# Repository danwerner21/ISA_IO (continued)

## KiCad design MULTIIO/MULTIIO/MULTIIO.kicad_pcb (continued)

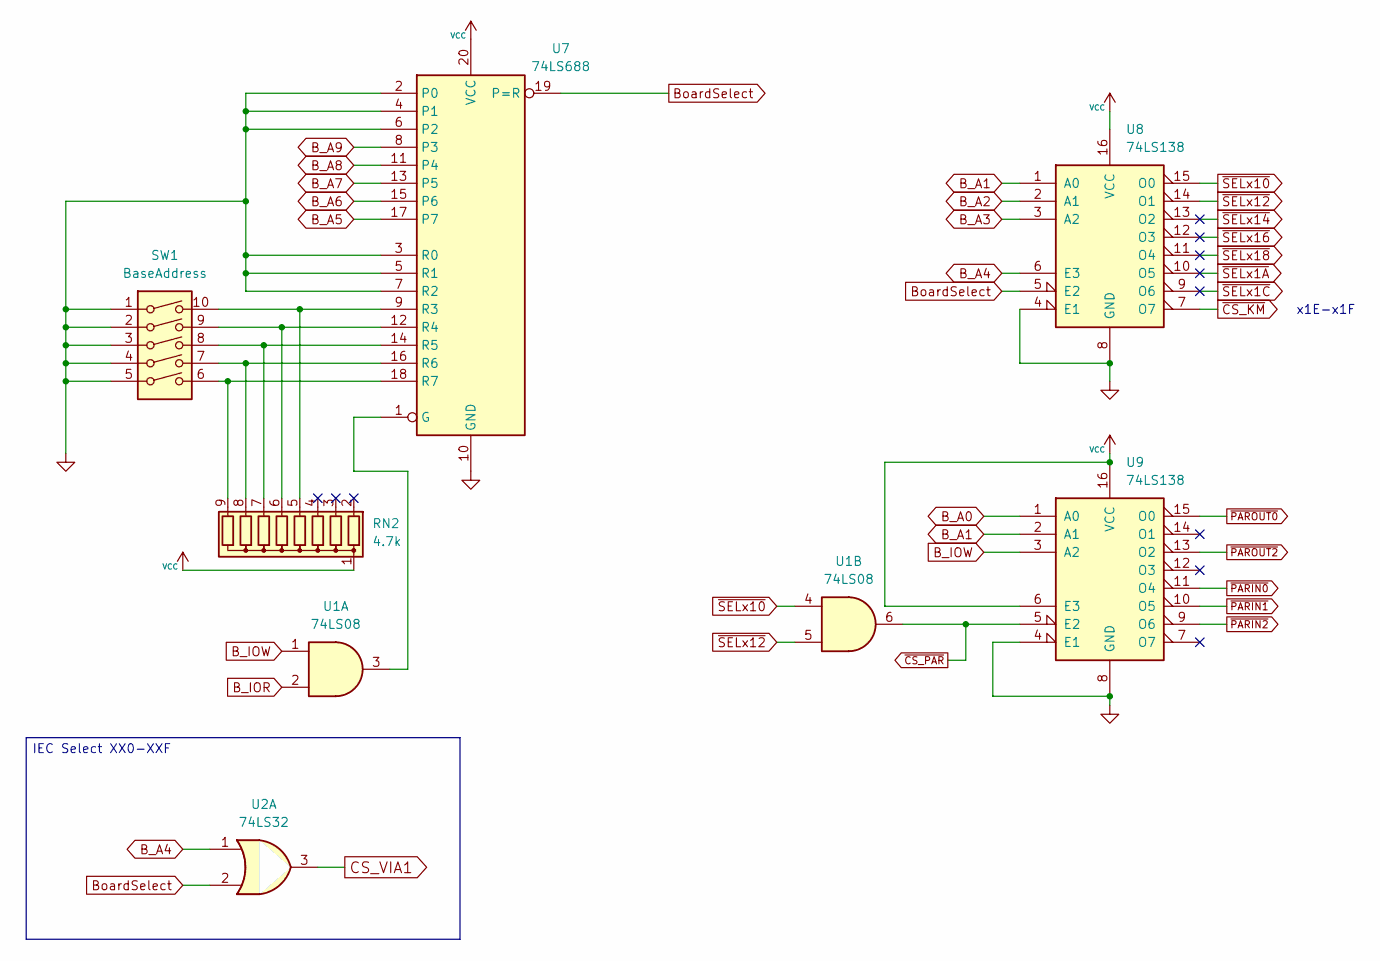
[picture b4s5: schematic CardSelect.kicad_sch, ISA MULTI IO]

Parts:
RN2: 4.7k; STD_DDW_SIP9
SW1: BaseAddress; STD_DDW_DIP10
U1: 74LS08; STD_DDW_DIP14
U2: 74LS32; STD_DDW_DIP14
U7: 74LS688; STD_DDW_DIP20
U8, U9: 74LS138; STD_DDW_DIP16

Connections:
B_A0: U9.1 (A0); also elsewhere on the board
B_A1: U8.1 (A0), U9.2 (A1); also elsewhere on the board
B_A2: U8.2 (A1); also elsewhere on the board
B_A3: U8.3 (A2); also elsewhere on the board
B_A4: U2.1, U8.6 (E3); also elsewhere on the board
B_A5: U7.17 (P7); also elsewhere on the board
B_A6: U7.15 (P6); also elsewhere on the board
B_A7: U7.13 (P5); also elsewhere on the board
B_A8: U7.11 (P4); also elsewhere on the board
B_A9: U7.8 (P3); also elsewhere on the board
B_IOR: U1.2; also elsewhere on the board
B_IOW: U1.1, U9.3 (A2); also elsewhere on the board
BoardSelect: U2.2, U7.19 (P=R), U8.5 (E2)
CS_VIA1: U2.3; also elsewhere on the board
GND: SW1.1, SW1.2, SW1.3, SW1.4, SW1.5, U7.2 (P0), U7.3 (R0), U7.4 (P1), U7.5 (R1), U7.6 (P2), U7.7 (R2), U7.10 (GND), U8.4 (E1), U8.8 (GND), U9.4 (E1), U9.8 (GND); also elsewhere on the board
unnamed: RN2.5 (R4), SW1.10, U7.9 (R3)
unnamed: RN2.6 (R5), SW1.9, U7.12 (R4)
unnamed: RN2.7 (R6), SW1.8, U7.14 (R5)
unnamed: RN2.8 (R7), SW1.7, U7.16 (R6)
unnamed: RN2.9 (R8), SW1.6, U7.18 (R7)
unnamed: U1.3, U7.1 (G)
VCC: RN2.1 (common), U7.20 (VCC), U8.16 (VCC), U9.6 (E3), U9.16 (VCC); also elsewhere on the board
~CS_KM: U8.7 (O7); also elsewhere on the board
~CS_PAR: U1.6, U9.5 (E2); also elsewhere on the board
~PARIN0: U9.11 (O4); also elsewhere on the board
~PARIN1: U9.10 (O5); also elsewhere on the board
~PARIN2: U9.9 (O6); also elsewhere on the board
~PAROUT0: U9.15 (O0); also elsewhere on the board
~PAROUT2: U9.13 (O2); also elsewhere on the board
~SELx1A: U8.10 (O5)
~SELx1C: U8.9 (O6)
~SELx10: U1.4, U8.15 (O0)
~SELx12: U1.5, U8.14 (O1)
~SELx14: U8.13 (O2)
~SELx16: U8.12 (O3)
~SELx18: U8.11 (O4)

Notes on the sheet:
IEC Select XX0-XXF
x1E-x1F

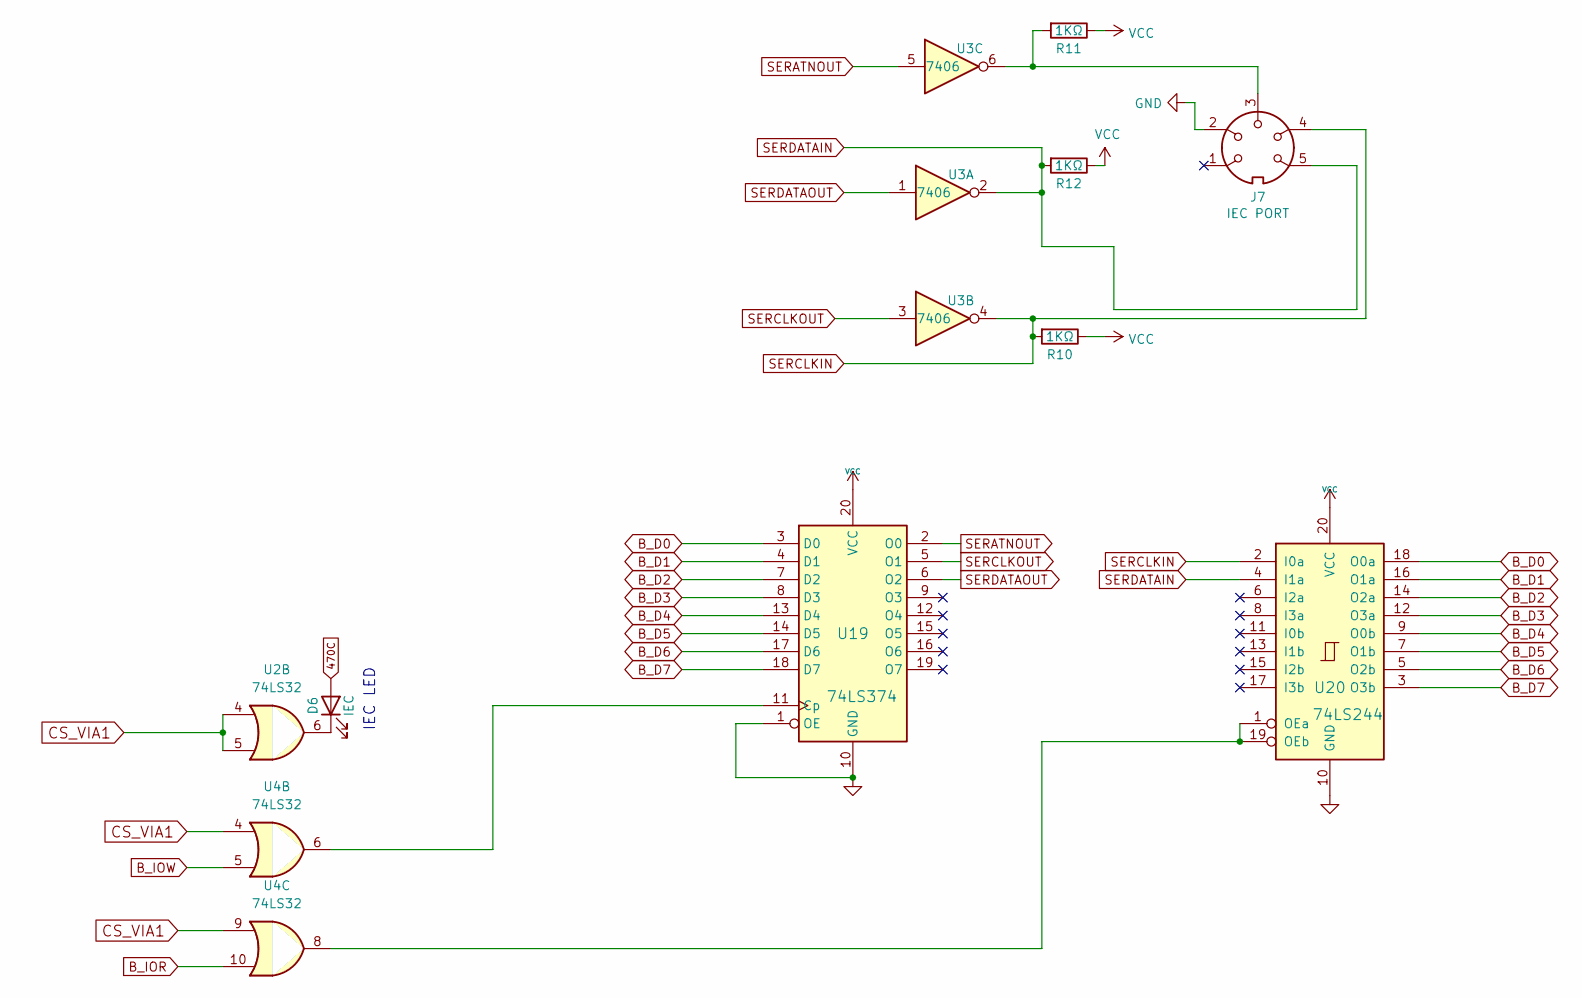
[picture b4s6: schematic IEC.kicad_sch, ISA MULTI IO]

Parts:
D6: IEC; STD_DDW_LED5
J7: IEC PORT; iec_din6
R10, R11, R12: 1KΩ; STD_DDW_RESISTOR
U2, U4: 74LS32; STD_DDW_DIP14
U3: 7406; STD_DDW_DIP14
U19: 74LS374; STD_DDW_DIP20
U20: 74LS244; STD_DDW_DIP20

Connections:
470C: D6.2 (A); also elsewhere on the board
B_D0: U19.3 (D0), U20.18 (O0a); also elsewhere on the board
B_D1: U19.4 (D1), U20.16 (O1a); also elsewhere on the board
B_D2: U19.7 (D2), U20.14 (O2a); also elsewhere on the board
B_D3: U19.8 (D3), U20.12 (O3a); also elsewhere on the board
B_D4: U19.13 (D4), U20.9 (O0b); also elsewhere on the board
B_D5: U19.14 (D5), U20.7 (O1b); also elsewhere on the board
B_D6: U19.17 (D6), U20.5 (O2b); also elsewhere on the board
B_D7: U19.18 (D7), U20.3 (O3b); also elsewhere on the board
B_IOR: U4.10; also elsewhere on the board
B_IOW: U4.5; also elsewhere on the board
CS_VIA1: U2.4, U2.5, U4.4, U4.9; also elsewhere on the board
GND: J7.2, U19.1 (OE), U19.10 (GND), U20.10 (GND); also elsewhere on the board
unnamed: D6.1 (K), U2.6
unnamed: J7.3, R11.2, U3.6
unnamed: U4.6, U19.11 (Cp)
unnamed: U4.8, U20.1 (OEa), U20.19 (OEb)
SERATNOUT: U3.5, U19.2 (O0)
SERCLKIN: J7.4, R10.2, U3.4, U20.2 (I0a)
SERCLKOUT: U3.3, U19.5 (O1)
SERDATAIN: J7.5, R12.2, U3.2, U20.4 (I1a)
SERDATAOUT: U3.1, U19.6 (O2)
VCC: R10.1, R11.1, R12.1, U19.20 (VCC), U20.20 (VCC); also elsewhere on the board

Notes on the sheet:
IEC LED

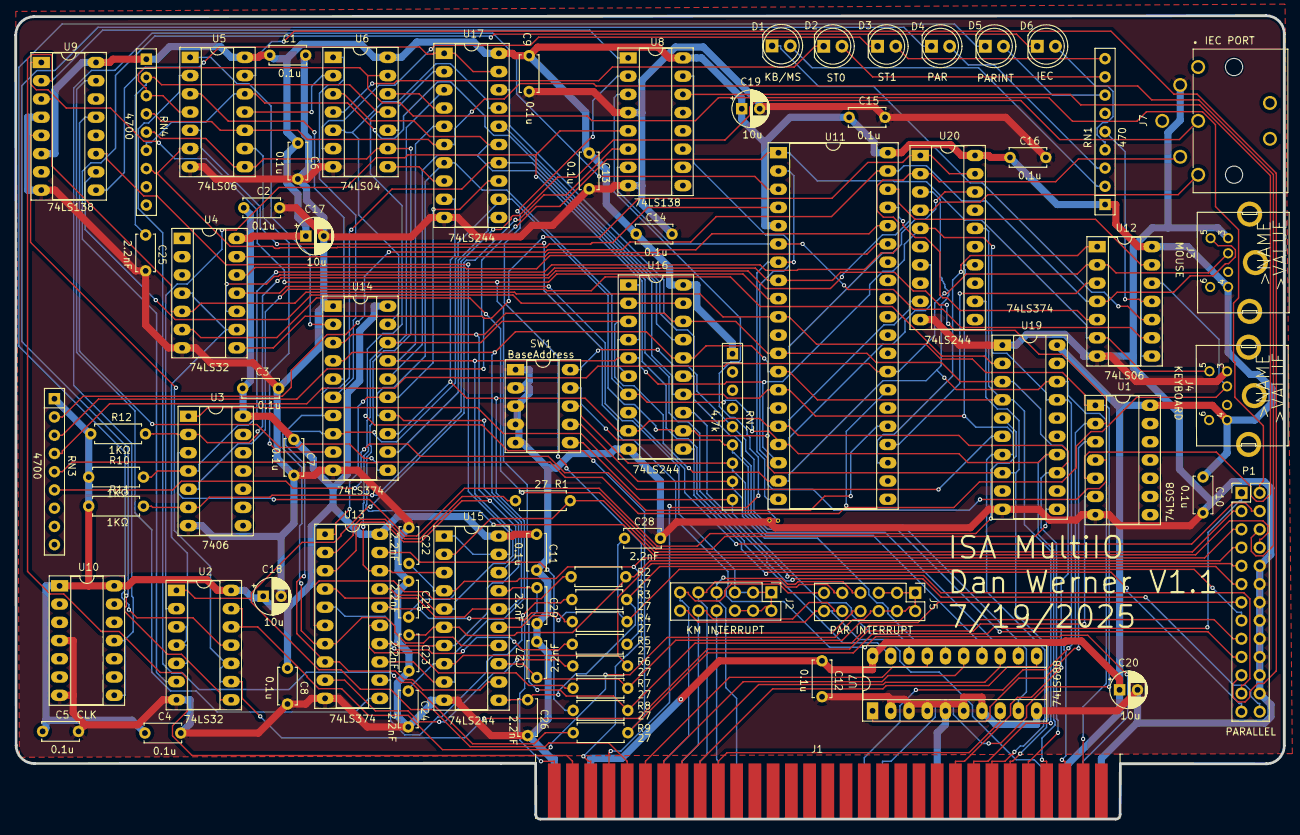
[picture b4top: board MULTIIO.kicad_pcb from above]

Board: 2 copper layers, 176.7 x 111.9 mm, 79 parts (0 on the bottom side), 122 nets.

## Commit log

2025-06-09 initial
2025-06-21 fix ESP layout issues
2025-06-29 ESPIO updates
2025-06-30 ESP firmware update
2025-07-20 multi io work
2026-01-18 video card updates
2026-02-01 version 1.1
2026-03-22 sound updates
2026-06-07 sound card working
2026-06-15 fix 80 col render
